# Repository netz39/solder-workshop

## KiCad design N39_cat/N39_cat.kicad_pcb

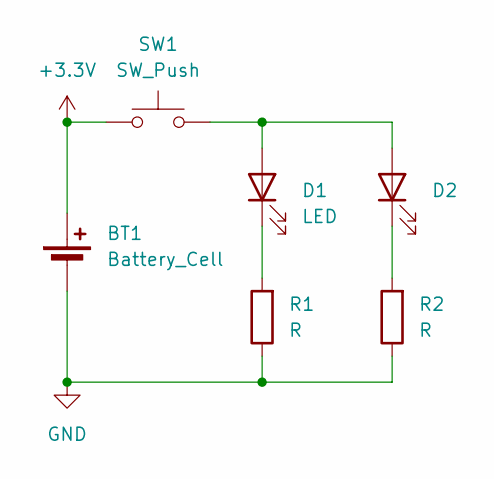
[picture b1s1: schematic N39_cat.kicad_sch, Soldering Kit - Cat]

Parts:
BT1: Battery_Cell; Battery Holder CR2032 BH-49B-5
D1, D2: LED; THT on SMD LED
R1, R2: R; THT on SMD Resistor
SW1: SW_Push; On Off Button

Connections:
+3.3V: BT1.1 (+), SW1.1
GND: BT1.2 (-), R1.1, R2.1
unnamed: D1.2 (A), D2.2 (A), SW1.2
unnamed: D1.1 (K), R1.2
unnamed: D2.1 (K), R2.2

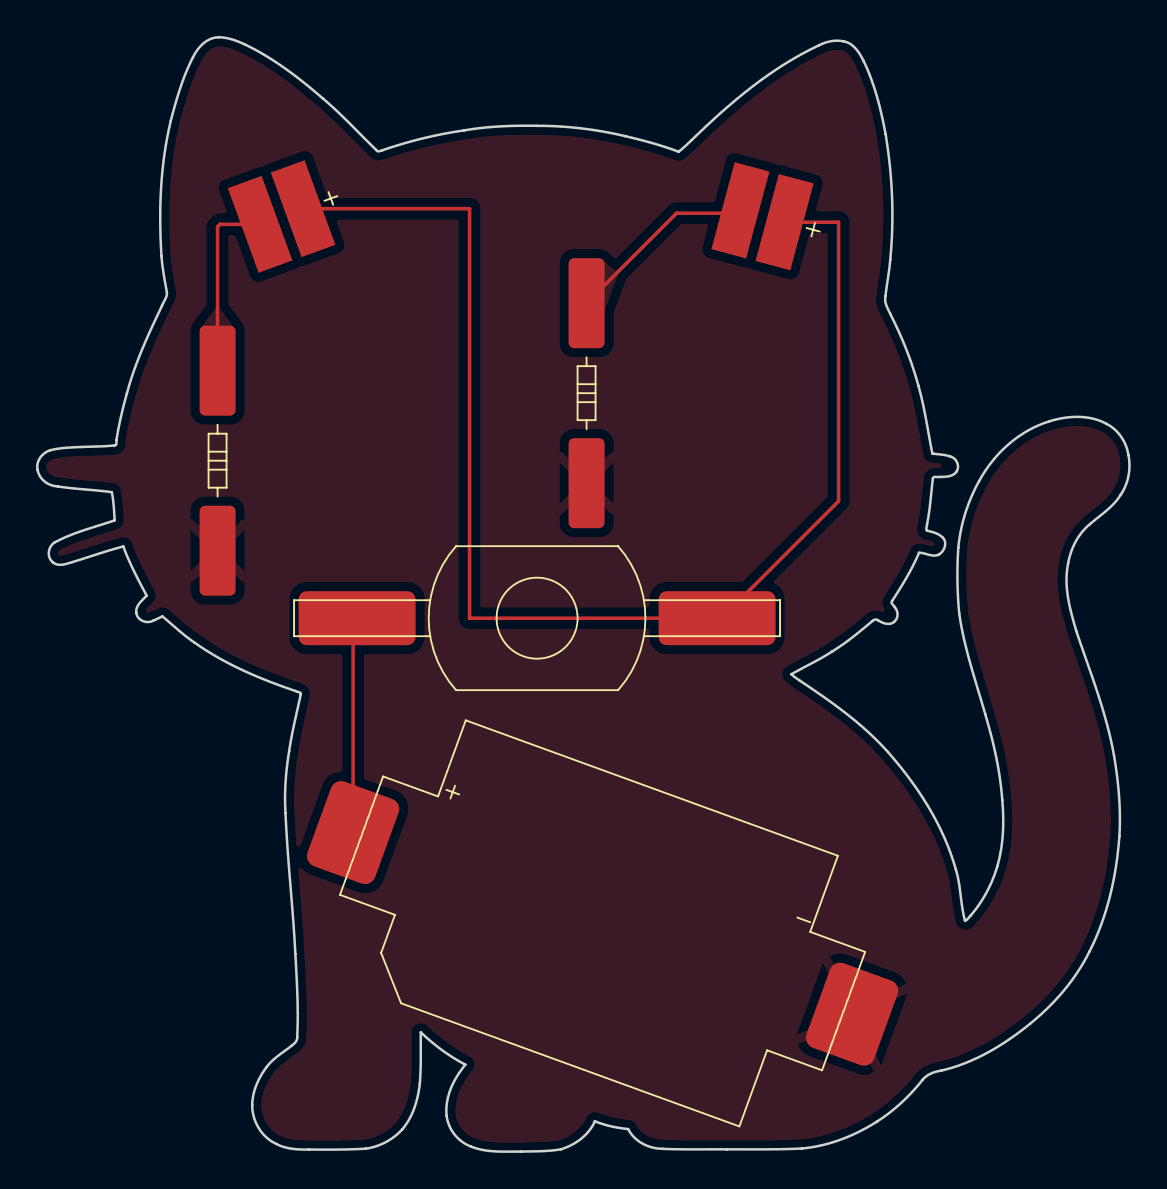
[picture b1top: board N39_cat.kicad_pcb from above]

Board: 2 copper layers, 60.7 x 61.9 mm, 6 parts (0 on the bottom side), 5 nets.

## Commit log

2025-05-24 Add octopus
2025-05-24 Add footprints
2025-05-24 Update placements
2025-05-24 added DXF files for the Octopus
2025-05-24 replace cat outline
2025-05-24 Add cats
2025-05-25 add DXF cat files
